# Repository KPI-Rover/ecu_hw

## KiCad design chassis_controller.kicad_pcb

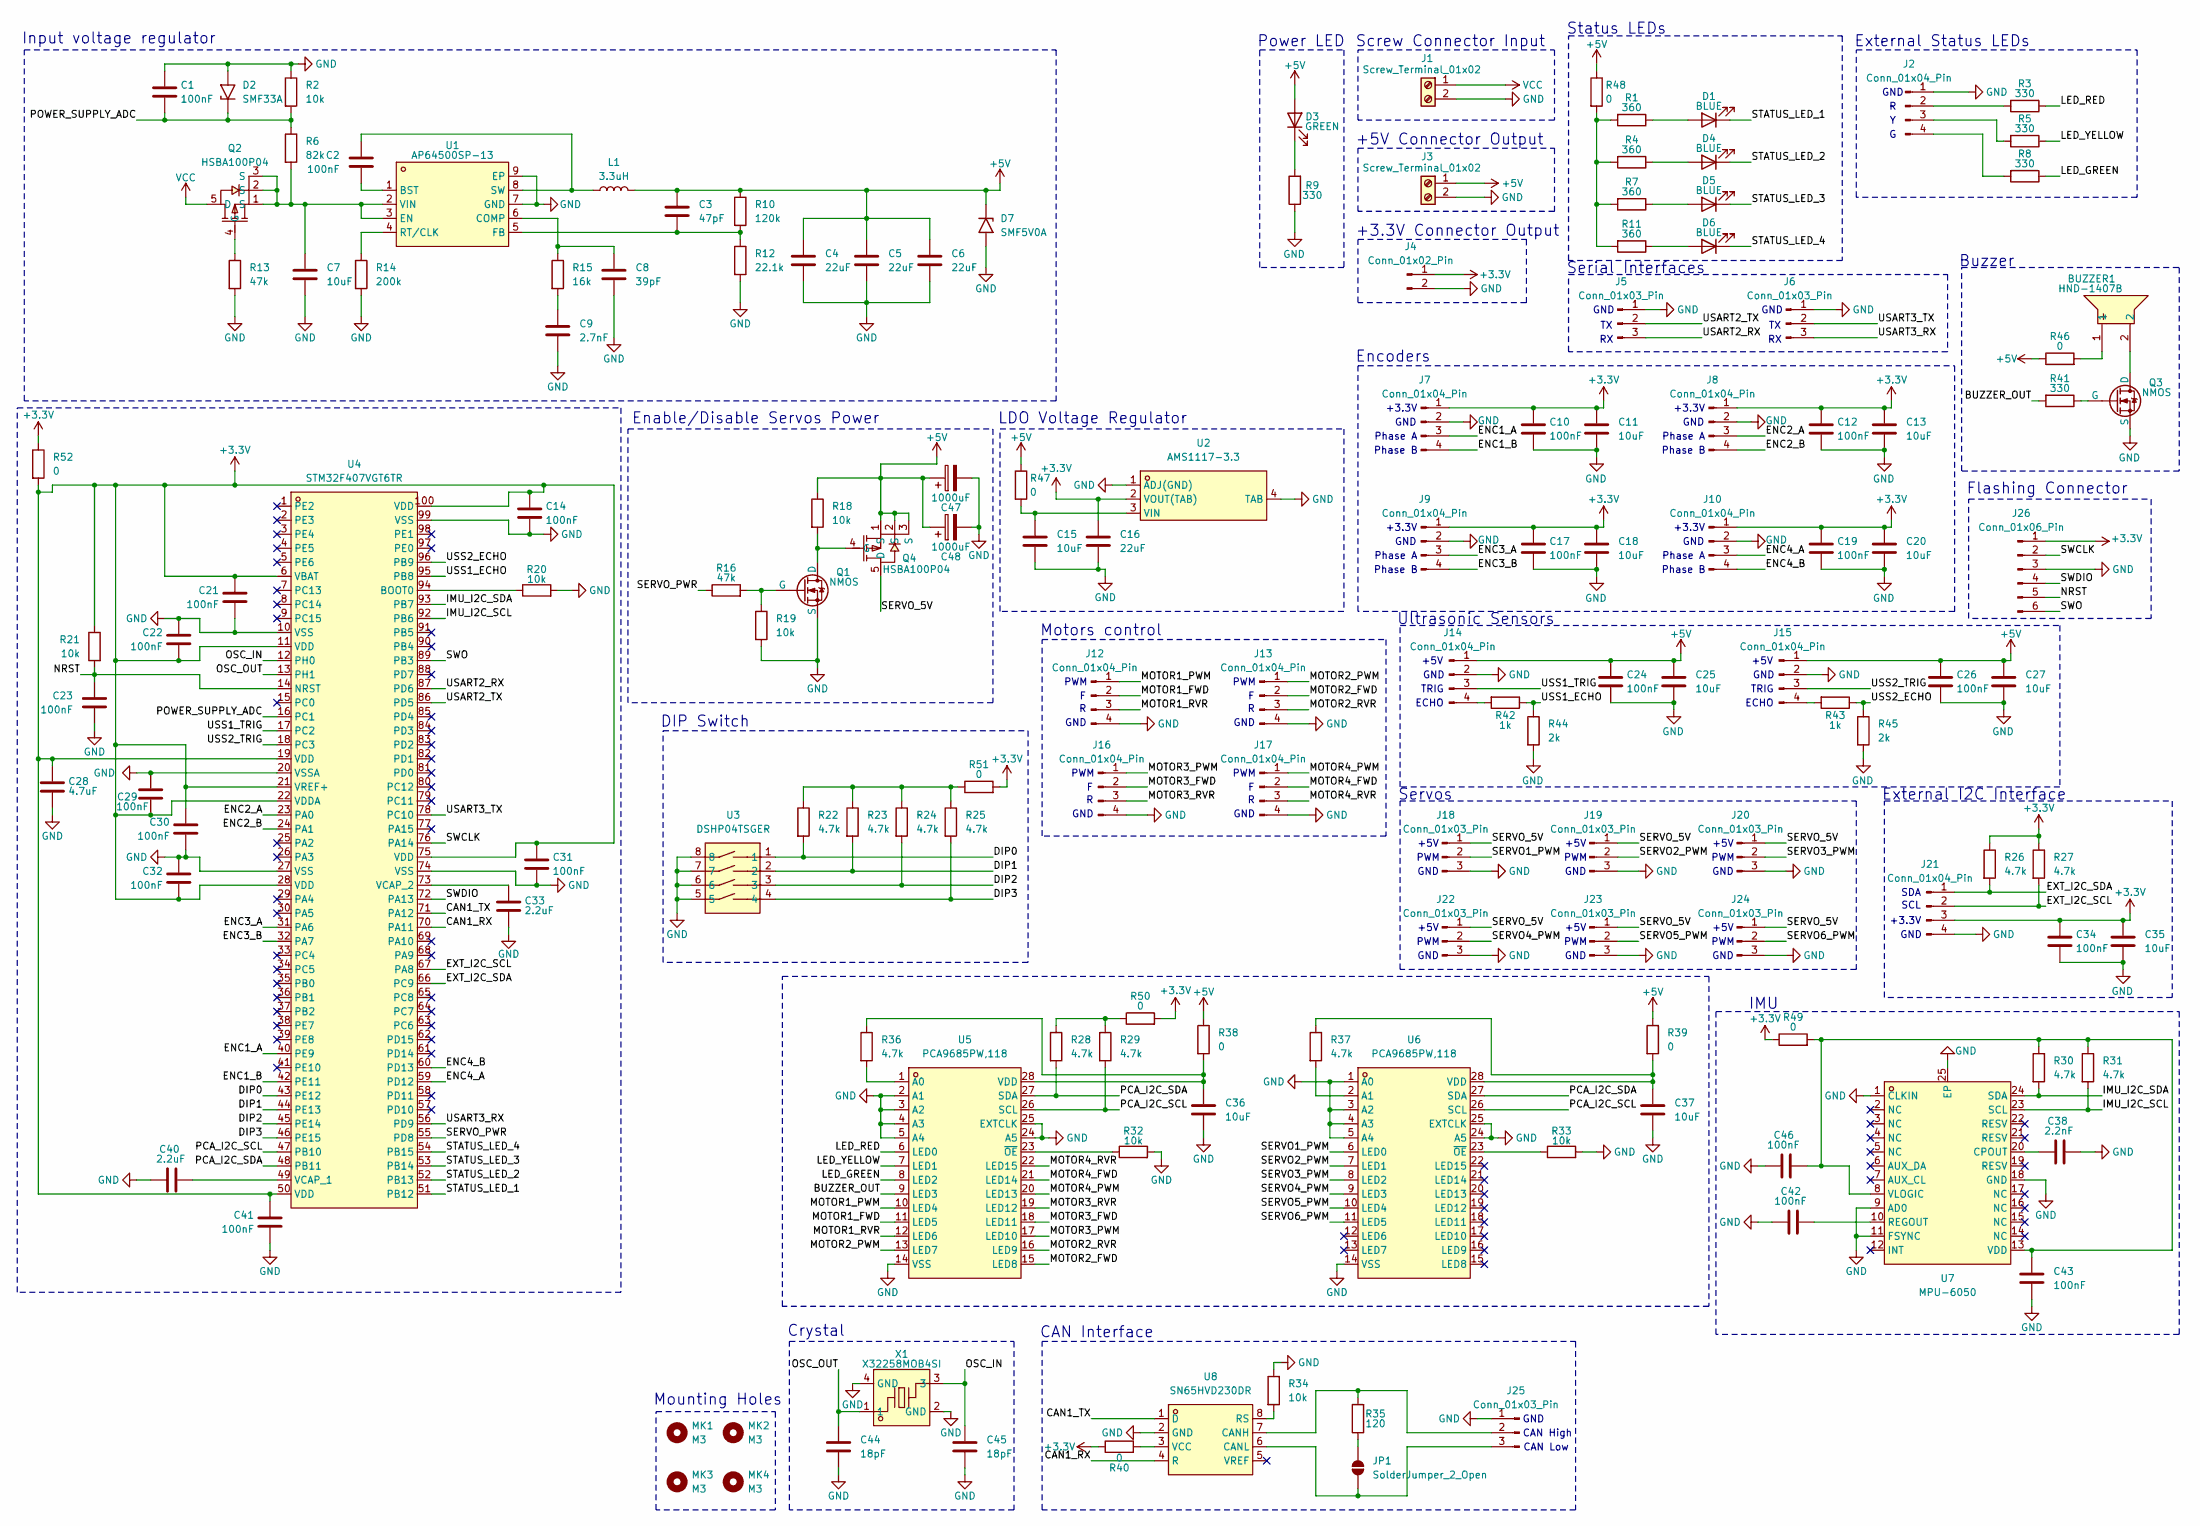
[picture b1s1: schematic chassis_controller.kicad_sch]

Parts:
BUZZER1: HND-1407B; BUZ-TH_BD14.1-P7.62-D1.0-FD; LCSC Part C115184
C1, C2, C10, C12, C14, C17, C19, C21, C22, C23, C24, C26, C29, C30, C31, C32, C34, C41, C42, C43, C46: 100nF; C_0805_2012Metric; LCSC Part C28233
C3: 47pF; C_0805_2012Metric; LCSC Part C107118
C4, C5, C6: 22uF; C_1206_3216Metric; LCSC Part C87996
C7, C15: 10uF; C_1206_3216Metric; LCSC Part C6119958
C8: 39pF; C_0805_2012Metric; LCSC Part C22470023
C9: 2.7nF; C_0805_2012Metric; LCSC Part C2918070
C11, C13, C18, C20, C25, C27, C35, C36, C37: 10uF; C_0805_2012Metric; LCSC Part C6119889
C16: 22uF; C_1206_3216Metric; LCSC Part C6119965
C28: 4.7uF; C_0805_2012Metric; LCSC Part C6119944
C33, C40: 2.2uF; C_0805_2012Metric; LCSC Part C125847
C38: 2.2nF; C_0805_2012Metric; LCSC Part C107146
C44, C45: 18pF; C_0805_2012Metric; LCSC Part C113825
C47, C48: 1000uF; CP_Radial_D10.0mm_P5.00mm; LCSC Part C439782
D1, D4, D5, D6: BLUE; LED_0805_2012Metric; LCSC Part C965817
D2: SMF33A; D_SMF; LCSC Part C37331473
D3: GREEN; LED_0805_2012Metric; LCSC Part C5875740
D7: SMF5V0A; D_SMF; LCSC Part C42387343
J1, J3: Screw_Terminal_01x02; CONN-TH_2P-P5.08; LCSC Part C3018698
J2, J7, J8, J9, J10, J12, J13, J14, J15, J16, J17, J21: Conn_01x04_Pin; JST_PH_B4B-PH-K_1x04_P2.00mm_Vertical; LCSC Part C131334
J4: Conn_01x02_Pin; JST_PH_B2B-PH-K_1x02_P2.00mm_Vertical; LCSC Part C131337
J5, J6, J18, J19, J20, J22, J23, J24, J25: Conn_01x03_Pin; JST_PH_B3B-PH-K_1x03_P2.00mm_Vertical; LCSC Part C131339
J26: Conn_01x06_Pin; JST_PH_B6B-PH-K_1x06_P2.00mm_Vertical; LCSC Part C131342
JP1: SolderJumper_2_Open; SolderJumper-2_P1.3mm_Open_Pad1.0x1.5mm
L1: 3.3uH; IND-SMD_L11.6-W10.1; LCSC Part C7587741
MK1, MK2, MK3, MK4: M3; MountingHole_3.2mm_M3_DIN965_Pad
Q1, Q3: NMOS; SOT-23; LCSC Part C347475
Q2, Q4: HSBA100P04; DFN-8_L5.7-W5.1-P1.27-LS6.1-BL-1; LCSC Part C2987717
R1, R4, R7, R11: 360; R_0805_2012Metric; LCSC Part C2930158
R2, R18, R19, R20, R21, R32, R33, R34: 10k; R_0805_2012Metric; LCSC Part C110775
R3, R5, R8, R9, R41: 330; R_0805_2012Metric; LCSC Part C2907321
R6: 82k; R_0805_2012Metric; LCSC Part C21571501
R10: 120k; R_0805_2012Metric; LCSC Part C103948
R12: 22.1k; R_0805_2012Metric; LCSC Part C2692772
R13, R16: 47k; R_0805_2012Metric; LCSC Part C2989281
R14: 200k; R_0805_2012Metric; LCSC Part C728645
R15: 16k; R_0805_2012Metric; LCSC Part C865809
R22, R23, R24, R25, R26, R27, R28, R29, R30, R31, R36, R37: 4.7k; R_0805_2012Metric; LCSC Part C2988931
R35: 120; R_0805_2012Metric; LCSC Part C17437
R38, R39, R40, R46, R47, R48, R49, R50, R51, R52: 0; R_0805_2012Metric; LCSC Part C17477
R42, R43: 1k; R_0805_2012Metric; LCSC Part C110774
R44, R45: 2k; R_0805_2012Metric; LCSC Part C2988894
U1: AP64500SP-13; SO-8_L4.9-W3.9-P1.27-LS6.0-BL-EP; LCSC Part C2070920
U2: AMS1117-3.3; SOT-223-4_L6.5-W3.5-P2.30-LS7.0-BR; LCSC Part C347222
U3: DSHP04TSGER; SW-SMD_8P-L6.7-W5.4-P1.27-LS8.4; LCSC Part C3293144
U4: STM32F407VGT6TR; LQFP-100_L14.0-W14.0-P0.50-LS16.0-BL; LCSC Part C919362
U5, U6: PCA9685PW,118; TSSOP-28_L9.7-W4.4-P0.65-LS6.4-TL; LCSC Part C2678753
U7: MPU-6050; QFN-24_L4.0-W4.0-P0.50-BL-EP2.7; LCSC Part C24112
U8: SN65HVD230DR; SOIC-8_L4.9-W3.9-P1.27-LS6.0-BL; LCSC Part C12084
X1: X32258MOB4SI; CRYSTAL-SMD_4P-L3.2-W2.5-BL; LCSC Part C2682775

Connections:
+3.3V: C10.1, C11.1, C12.1, C13.1, C14.1, C16.1, C17.1, C18.1, C19.1, C20.1, C21.1, C22.2, C28.2, C29.2, C30.1, C31.1, C32.2, C34.1, C35.1, C41.1, J4.1, J7.1, J8.1, J9.1, J10.1, J21.3, J26.1, R21.1, R26.1, R27.1, R40.1, R49.1, R50.2, R51.2, R52.1, R52.2, U2.2 (VOUT(TAB)), U4.6 (VBAT), U4.11 (VDD), U4.19 (VDD), U4.21 (VREF+), U4.22 (VDDA), U4.28 (VDD), U4.50 (VDD), U4.75 (VDD), U4.100 (VDD)
+5V: C3.1, C4.1, C5.1, C6.1, C24.1, C25.1, C26.1, C27.1, C47.1, C48.1, D3.2 (A), D7.1 (A1), J3.1, J14.1, J15.1, L1.2, Q4.1 (S), Q4.2 (S), Q4.3 (S), R10.1, R18.1, R38.1, R39.1, R46.1, R47.1, R48.1
/BUZZER_OUT: R41.2, U5.9 (LED3)
/CAN1_RX: U4.70 (PA11), U8.4 (R)
/CAN1_TX: U4.71 (PA12), U8.1 (D)
/DIP0: R22.2, U3.1, U4.43 (PE12)
/DIP1: R23.2, U3.2, U4.44 (PE13)
/DIP2: R24.2, U3.3, U4.45 (PE14)
/DIP3: R25.2, U3.4, U4.46 (PE15)
/ENC1_A: J7.3, U4.40 (PE9)
/ENC1_B: J7.4, U4.42 (PE11)
/ENC2_A: J8.3, U4.23 (PA0)
/ENC2_B: J8.4, U4.24 (PA1)
/ENC3_A: J9.3, U4.31 (PA6)
/ENC3_B: J9.4, U4.32 (PA7)
/ENC4_A: J10.3, U4.59 (PD12)
/ENC4_B: J10.4, U4.60 (PD13)
/EXT_I2C_SCL: J21.2, R27.2, U4.67 (PA8)
/EXT_I2C_SDA: J21.1, R26.2, U4.66 (PC9)
/IMU_I2C_SCL: R31.2, U4.92 (PB6), U7.23 (SCL)
/IMU_I2C_SDA: R30.2, U4.93 (PB7), U7.24 (SDA)
/LED_GREEN: R8.1, U5.8 (LED2)
/LED_RED: R3.1, U5.6 (LED0)
/LED_YELLOW: R5.1, U5.7 (LED1)
/MOTOR1_FWD: J12.2, U5.11 (LED5)
/MOTOR1_PWM: J12.1, U5.10 (LED4)
/MOTOR1_RVR: J12.3, U5.12 (LED6)
/MOTOR2_FWD: J13.2, U5.15 (LED8)
/MOTOR2_PWM: J13.1, U5.13 (LED7)
/MOTOR2_RVR: J13.3, U5.16 (LED9)
/MOTOR3_FWD: J16.2, U5.18 (LED11)
/MOTOR3_PWM: J16.1, U5.17 (LED10)
/MOTOR3_RVR: J16.3, U5.19 (LED12)
/MOTOR4_FWD: J17.2, U5.21 (LED14)
/MOTOR4_PWM: J17.1, U5.20 (LED13)
/MOTOR4_RVR: J17.3, U5.22 (LED15)
/NRST: C23.1, J26.5, R21.2, U4.14 (NRST)
/OSC_IN: C45.1, U4.12 (PH0), X1.3
/OSC_OUT: C44.1, U4.13 (PH1), X1.1
/PCA_I2C_SCL: R29.2, U4.47 (PB10), U5.26 (SCL), U6.26 (SCL)
/PCA_I2C_SDA: R28.2, U4.48 (PB11), U5.27 (SDA), U6.27 (SDA)
/POWER_SUPPLY_ADC: C1.2, D2.1 (A1), R2.2, R6.1, U4.16 (PC1)
/SERVO1_PWM: J18.2, U6.6 (LED0)
/SERVO2_PWM: J19.2, U6.7 (LED1)
/SERVO3_PWM: J20.2, U6.8 (LED2)
/SERVO4_PWM: J22.2, U6.9 (LED3)
/SERVO5_PWM: J23.2, U6.10 (LED4)
/SERVO6_PWM: J24.2, U6.11 (LED5)
/SERVO_5V: J18.1, J19.1, J20.1, J22.1, J23.1, J24.1, Q4.5 (D)
/SERVO_PWR: R16.1, U4.55 (PD8)
/STATUS_LED_1: D1.1 (K), U4.51 (PB12)
/STATUS_LED_2: D4.1 (K), U4.52 (PB13)
/STATUS_LED_3: D5.1 (K), U4.53 (PB14)
/STATUS_LED_4: D6.1 (K), U4.54 (PB15)
/SWCLK: J26.2, U4.76 (PA14)
/SWDIO: J26.4, U4.72 (PA13)
/SWO: J26.6, U4.89 (PB3)
/USART2_RX: J5.3, U4.87 (PD6)
/USART2_TX: J5.2, U4.86 (PD5)
/USART3_RX: J6.3, U4.56 (PD9)
/USART3_TX: J6.2, U4.78 (PC10)
/USS1_ECHO: R42.1, R44.1, U4.95 (PB8)
/USS1_TRIG: J14.3, U4.17 (PC2)
/USS2_ECHO: R43.1, R45.1, U4.96 (PB9)
/USS2_TRIG: J15.3, U4.18 (PC3)
GND: C1.1, C4.2, C5.2, C6.2, C7.2, C8.2, C9.2, C10.2, C11.2, C12.2, C13.2, C14.2, C15.2, C16.2, C17.2, C18.2, C19.2, C20.2, C21.2, C22.1, C23.2, C24.2, C25.2, C26.2, C27.2, C28.1, C29.1, C30.2, C31.2, C32.1, C33.1, C34.2, C35.2, C36.2, C37.2, C38.2, C40.1, C41.2, C42.1, C43.2, C44.2, C45.2, C46.1, C47.2, C48.2, D2.2 (A2), D7.2 (A2), J1.2, J2.1, J3.2, J4.2, J5.1, J6.1, J7.2, J8.2, J9.2, J10.2, J12.4, J13.4, J14.2, J15.2, J16.4, J17.4, J18.3, J19.3, J20.3, J21.4, J22.3, J23.3, J24.3, J25.1, J26.3, Q1.3 (S), Q3.3 (S), R2.1, R9.1, R12.2, R13.2, R14.2, R19.2, R20.2, R32.2, R33.2, R34.1, R44.2, R45.2, U1.7 (GND), U1.9 (EP), U2.1 (ADJ(GND)), U2.4 (TAB), U3.5, U3.6, U3.7, U3.8, U4.10 (VSS), U4.20 (VSSA), U4.27 (VSS), U4.74 (VSS), U4.99 (VSS), U5.2 (A1), U5.3 (A2), U5.4 (A3), U5.5 (A4), U5.14 (VSS), U5.24 (A5), U5.25 (EXTCLK), U6.1 (A0), U6.3 (A2), U6.4 (A3), U6.5 (A4), U6.14 (VSS), U6.24 (A5), U6.25 (EXTCLK), U7.1 (CLKIN), U7.9 (AD0), U7.11 (FSYNC), U7.18 (GND), U7.25 (EP), U8.2 (GND), X1.2 (GND), X1.4 (GND)
unnamed: BUZZER1.1, R46.2
unnamed: C9.1, R15.2
unnamed: D1.2 (A), R1.1
unnamed: D3.1 (K), R9.2
unnamed: D4.2 (A), R4.1
unnamed: D5.2 (A), R7.1
unnamed: D6.2 (A), R11.1
unnamed: J2.2, R3.2
unnamed: J2.3, R5.2
unnamed: J2.4, R8.2
unnamed: J14.4, R42.2
unnamed: J15.4, R43.2
unnamed: J25.2, R35.2, U8.7 (CANH)
unnamed: J25.3, JP1.2 (B), U8.6 (CANL)
unnamed: JP1.1 (A), R35.1
unnamed: Q1.1 (D), Q4.4 (G), R18.2
unnamed: Q1.2 (G), R16.2, R19.1
unnamed: Q2.4 (G), R13.1
unnamed: BUZZER1.2, Q3.1 (D)
unnamed: Q3.2 (G), R41.1
unnamed: R1.2, R4.2, R7.2, R11.2, R48.2
unnamed: R22.1, R23.1, R24.1, R25.1, R51.1
unnamed: R28.1, R29.1, R50.1
unnamed: C2.2, U1.1 (BST)
unnamed: C8.1, R15.1, U1.6 (COMP)
unnamed: C7.1, Q2.1 (S), Q2.2 (S), Q2.3 (S), R6.2, U1.2 (VIN), U1.3 (EN)
unnamed: C3.2, R10.2, R12.1, U1.5 (FB)
unnamed: R14.1, U1.4 (RT/CLK)
unnamed: C2.1, L1.1, U1.8 (SW)
unnamed: C15.1, R47.2, U2.3 (VIN)
unnamed: R20.1, U4.94 (BOOT0)
unnamed: C40.2, U4.49 (VCAP_1)
unnamed: C33.2, U4.73 (VCAP_2)
unnamed: R36.2, U5.1 (A0)
unnamed: C36.1, R36.1, R38.2, U5.28 (VDD)
unnamed: R32.1, U5.23 (~OE)
unnamed: R37.2, U6.2 (A1)
unnamed: C37.1, R37.1, R39.2, U6.28 (VDD)
unnamed: R33.1, U6.23 (~OE)
unnamed: C38.1, U7.20 (CPOUT)
unnamed: C42.2, U7.10 (REGOUT)
unnamed: C43.1, C46.2, R30.1, R31.1, R49.2, U7.8 (VLOGIC), U7.13 (VDD)
unnamed: R34.2, U8.8 (RS)
unnamed: R40.2, U8.3 (VCC)
VCC: J1.1, Q2.5 (D)

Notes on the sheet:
GND
Screw Connector Input
Phase B
PWM
Flashing Connector
External I2C Interface
Status LEDs
+5V
Power LED
Phase A
+3.3V
+5V Connector Output
External Status LEDs
Mounting Holes
SDA
Buzzer
IMU
CAN Low
CAN Interface
Enable/Disable Servos Power
Serial Interfaces
DIP Switch
Encoders
Ultrasonic Sensors
LDO Voltage Regulator
ECHO
TRIG
+3.3V Connector Output
Crystal
Motors control
CAN High
Input voltage regulator
Servos
SCL

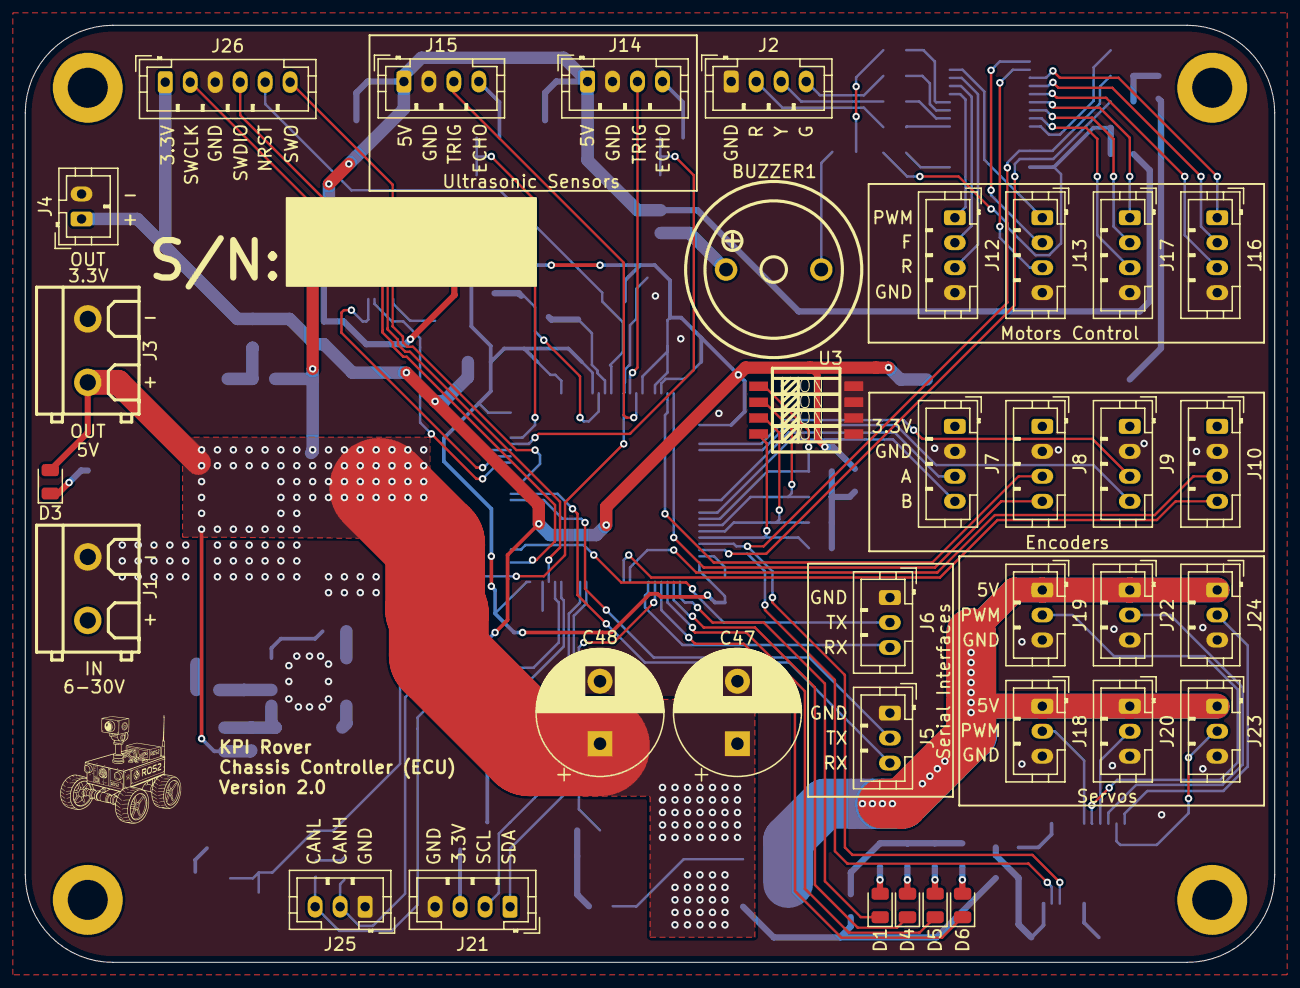
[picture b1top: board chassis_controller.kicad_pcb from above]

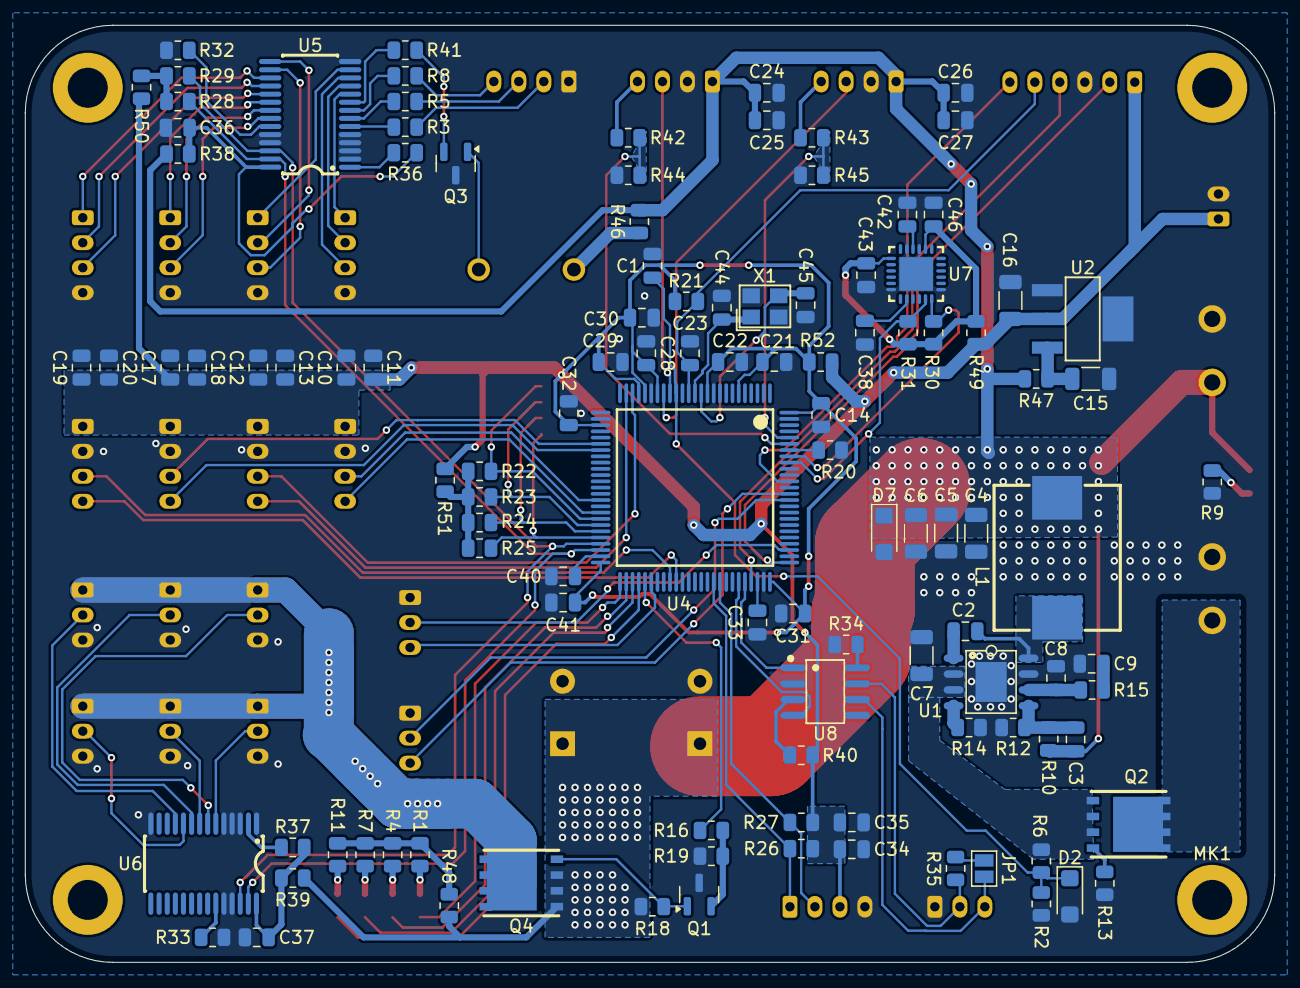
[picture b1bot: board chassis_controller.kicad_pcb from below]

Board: 2 copper layers, 100.0 x 75.0 mm, 150 parts (113 on the bottom side), 111 nets.

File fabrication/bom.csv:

"Reference","Qty","Value","LCSC Part"
"BUZZER1","1","HND-1407B","C115184"
"C1,C2,C10,C12,C14,C17,C19,C21,C22,C23,C24,C26,C29,C30,C31,C32,C34,C41,C42,C43,C46","21","100nF","C28233"
"C3","1","47pF","C107118"
"C4,C5,C6","3","22uF","C87996"
"C7,C15","2","10uF","C6119958"
"C8","1","39pF","C22470023"
"C9","1","2.7nF","C2918070"
"C11,C13,C18,C20,C25,C27,C35,C36,C37","9","10uF","C6119889"
"C16","1","22uF","C6119965"
"C28","1","4.7uF","C6119944"
"C33,C40","2","2.2uF","C125847"
"C38","1","2.2nF","C107146"
"C44,C45","2","18pF","C113825"
"C47,C48","2","1000uF","C439782"
"D1,D4,D5,D6","4","BLUE","C965817"
"D2","1","SMF33A","C37331473"
"D3","1","GREEN","C5875740"
"D7","1","SMF5V0A","C42387343"
"J1,J3","2","Screw_Terminal_01x02","C3018698"
"J2,J7,J8,J9,J10,J12,J13,J14,J15,J16,J17,J21","12","Conn_01x04_Pin","C131334"
"J4","1","Conn_01x02_Pin","C131337"
"J5,J6,J18,J19,J20,J22,J23,J24,J25","9","Conn_01x03_Pin","C131339"
"J26","1","Conn_01x06_Pin","C131342"
"JP1,MK1,MK2,MK3,MK4","5","M3,SolderJumper_2_Open",""
"L1","1","3.3uH","C7587741"
"Q1,Q3","2","NMOS","C347475"
"Q2,Q4","2","HSBA100P04","C2987717"
"R1,R4,R7,R11","4","360","C2930158"
"R2,R18,R19,R20,R21,R32,R33,R34","8","10k","C110775"
"R3,R5,R8,R9,R41","5","330","C2907321"
"R6","1","82k","C21571501"
"R10","1","120k","C103948"
"R12","1","22.1k","C2692772"
"R13,R16","2","47k","C2989281"
"R14","1","200k","C728645"
"R15","1","16k","C865809"
"R22,R23,R24,R25,R26,R27,R28,R29,R30,R31,R36,R37","12","4.7k","C2988931"
"R35","1","120","C17437"
"R38,R39,R40,R46,R47,R48,R49,R50,R51,R52","10","0","C17477"
"R42,R43","2","1k","C110774"
"R44,R45","2","2k","C2988894"
"U1","1","AP64500SP-13","C2070920"
"U2","1","AMS1117-3.3","C347222"
"U3","1","DSHP04TSGER","C3293144"
"U4","1","STM32F407VGT6TR","C919362"
"U5,U6","2","PCA9685PW,118","C2678753"
"U7","1","MPU-6050","C24112"
"U8","1","SN65HVD230DR","C12084"
"X1","1","X32258MOB4SI","C2682775"

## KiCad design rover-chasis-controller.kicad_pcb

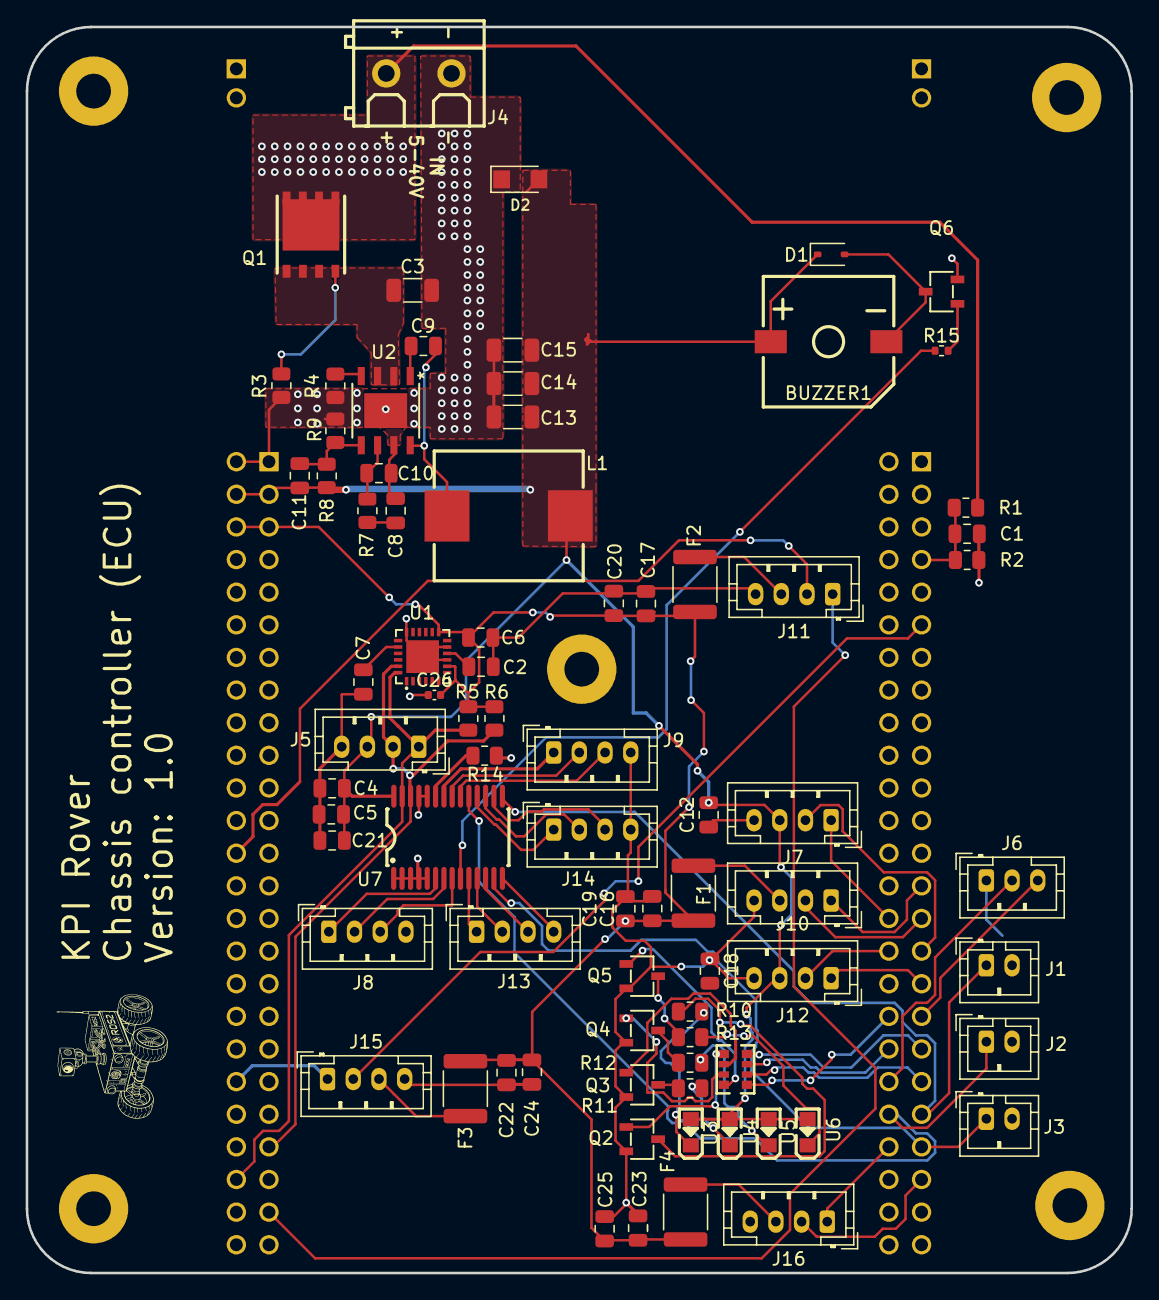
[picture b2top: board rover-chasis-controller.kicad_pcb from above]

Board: 2 copper layers, 86.0 x 97.0 mm, 85 parts (1 on the bottom side), 70 nets.

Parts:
BUZZER1: YS-SBZ9650DYB05_C409830; BUZ-SMD_L9.6-W9.6-LS10.0-R
C1, C2, C4, C6, C9, C12, C18, C19, C20, C24, C25: 0.1uF; C_0805_2012Metric
C3: 10uFx50V; C_1206_3216Metric
C5, C16, C17, C21, C22, C23: 10uFx16V; C_0805_2012Metric
C7: 2.2nF; C_0805_2012Metric
C8: 2.7nF; C_0805_2012Metric
C10: 39pF; C_0805_2012Metric
C11: 47pF; C_0805_2012Metric
C13, C14, C15: 22uF; C_1206_3216Metric
C26: 10nF; C_0402_1005Metric
D1: D; D_SOD-323
D2: SMF5V0A; D_SMF
F1, F2, F3, F4: Fuse; Fuse_1812_4532Metric
J1: External LED (Green); JST_PH_B2B-PH-K_1x02_P2.00mm_Vertical
J2: External LED (Yellow); JST_PH_B2B-PH-K_1x02_P2.00mm_Vertical
J3: External LED (Red); JST_PH_B2B-PH-K_1x02_P2.00mm_Vertical
J4: Screw_Terminal_01x02; CONN-TH_2P-P5.08
J5: Compass Connection (I2C); JST_PH_B4B-PH-K_1x04_P2.00mm_Vertical
J6: TTL; JST_PH_B3B-PH-K_1x03_P2.00mm_Vertical
J7, J12: Ultrasonic Sensor Inputs; JST_PH_B4B-PH-K_1x04_P2.00mm_Vertical
J8, J9, J13, J14: Motor control; JST_PH_B4B-PH-K_1x04_P2.00mm_Vertical
J10, J11, J15, J16: Encoder; JST_PH_B4B-PH-K_1x04_P2.00mm_Vertical
L1: 3.3uH; IND-SMD_L11.6-W10.1
MK1, MK2, MK3, MK4, MK5: M2.5; MountingHole_2.7mm_M2.5_Pad
Q1: HSBA100P04_C2987717; DFN-8_L5.7-W5.1-P1.27-LS6.1-BL-1
Q2, Q3, Q4, Q5, Q6: MMBT3904_C181119; SOT-23-3_L2.9-W1.6-P1.90-LS2.8-BR
R1: 100k; R_0805_2012Metric
R2: 22k; R_0805_2012Metric
R3: 47k; R_0805_2012Metric
R4: 200k; R_0805_2012Metric
R5, R6: 4.3k; R_0805_2012Metric
R7: 16k; R_0805_2012Metric
R8: 120k; R_0805_2012Metric
R9: 22.1k; R_0805_2012Metric
R10, R11, R12, R13: 220; R_0805_2012Metric
R14: 10k; R_0805_2012Metric
R15: 1k; R_0402_1005Metric
RN1: 4D03WGJ0102T5E (1k); RES-ARRAY-SMD_0603-8P-L3.2-W1.6-BL
TB1: STM32F4DISCOVERY; MODULE_STM32F4DISCOVERY
U1: MPU-6050_C24112; QFN-24_L4.0-W4.0-P0.50-BL-EP2.6
U2: AP64500; AP64500SP-13
U3, U4, U5, U6: APT2012LVBC/D; LED-SMD_L2.0-W1.3-R-RD
U7: PCA9685PW,118; TSSOP-28_L9.7-W4.4-P0.65-LS6.4-TL

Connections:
/BUZZER_OUT: R15.1, U7.9 (LED3)
/ENC1_A: J10.1, TB1.P1_27 (PE9)
/ENC1_B: J10.2, TB1.P1_29 (PE11)
/ENC2_A: J15.1, TB1.P2_40 (PA15)
/ENC2_B: J15.2, TB1.P1_11 (PA1)
/ENC3_A: J11.1, TB1.P2_47 (PC6)
/ENC3_B: J11.2, TB1.P2_26 (PB5)
/ENC4_A: J16.1, TB1.P1_44 (PD12)
/ENC4_B: J16.2, TB1.P1_45 (PD13)
/LED_BLUE_1: RN1.8, TB1.P1_37 (PB13)
/LED_BLUE_2: RN1.7, TB1.P1_38 (PB14)
/LED_BLUE_3: RN1.6, TB1.P1_39 (PB15)
/LED_BLUE_4: RN1.5, TB1.P1_36 (PB12)
/LED_Collector_1: Q2.3, R10.2
/LED_Collector_2: Q3.3, R11.2
/LED_Collector_3: Q4.3, R12.2
/LED_Collector_4: Q5.3, R13.2
/LED_GREEN: J1.1, TB1.P1_41 (PD9), U7.15 (LED8)
/LED_RED: J3.1, TB1.P1_43 (PD11), U7.13 (LED7)
/LED_YELLOW: J2.1, TB1.P1_42 (PD10), U7.19 (LED12)
/MOTOR1_FWD: J8.2, U7.7 (LED1)
/MOTOR1_PWM: J8.1, U7.6 (LED0)
/MOTOR1_RVR: J8.3, U7.8 (LED2)
/MOTOR2_FWD: J13.2, U7.11 (LED5)
/MOTOR2_PWM: J13.1, U7.10 (LED4)
/MOTOR2_RVR: J13.3, U7.12 (LED6)
/MOTOR3_FWD: J9.2, U7.21 (LED14)
/MOTOR3_PWM: J9.1, U7.22 (LED15)
/MOTOR3_RVR: J9.3, U7.20 (LED13)
/MOTOR4_FWD: J14.2, U7.17 (LED10)
/MOTOR4_PWM: J14.1, U7.18 (LED11)
/MOTOR4_RVR: J14.3, U7.16 (LED9)
/POWER_SUPPLY_ADC: C1.2, R1.2, R2.1, TB1.P1_7 (PC1)
/SCL: J5.2, R6.2, TB1.P2_43 (PA8), U1.23 (SCL), U7.26 (SCL)
/SDA: J5.1, R5.2, TB1.P2_46 (PC9), U1.24 (SDA), U7.27 (SDA)
/TTL_RX: J6.3, TB1.P1_35 (PB11)
/TTL_TX: J6.2, TB1.P1_40 (PD8)
/US_SENSOR1_ECHO: J7.2, TB1.P1_31 (PE13)
/US_SENSOR1_TRIG: J7.1, TB1.P1_30 (PE12)
/US_SENSOR2_ECHO: J12.2, TB1.P1_32 (PE14)
/US_SENSOR2_TRIG: J12.1, TB1.P1_33 (PE15)
/transistor_array4/B1: Q2.1, RN1.1
/transistor_array4/B2: Q3.1, RN1.2
/transistor_array4/B3: Q4.1, RN1.3
/transistor_array4/B4: Q5.1, RN1.4
GND: C1.1, C2.1, C3.2, C4.1, C5.1, C6.1, C7.2, C8.2, C10.2, C12.1, C13.2, C14.2, C15.2, C16.1, C17.1, C18.1, C19.1, C20.1, C21.2, C22.1, C23.1, C24.1, C25.1, C26.1, D2.1 (A1), J1.2, J2.2, J3.2, J4.2, J5.4, J6.1, J7.4, J8.4, J9.4, J10.4, J11.4, J12.4, J13.4, J14.4, J15.4, J16.4, Q2.2, Q3.2, Q4.2, Q5.2, Q6.2, R2.2, R3.2, R4.2, R9.2, R14.1, TB1.P1_1 (GND), TB1.P1_2 (GND), TB1.P1_5 (GND), TB1.P1_23 (GND), TB1.P1_49 (GND), TB1.P1_50 (GND), TB1.P2_1 (GND), TB1.P2_2 (GND), TB1.P2_49 (GND), TB1.P2_50 (GND), U1.9 (AD0), U1.11 (FSYNC), U1.18 (GND), U1.25 (EP), U2.7 (GND), U7.1 (A0), U7.2 (A1), U7.3 (A2), U7.4 (A3), U7.5 (A4), U7.14 (VSS), U7.24 (A5), U7.25 (EXTCLK)
unnamed: BUZZER1.2 (-), D1.2 (A), Q6.3
unnamed: C8.1, R7.2
unnamed: F1.1, J10.3
unnamed: F2.1, J11.3
unnamed: F3.1, J15.3
unnamed: F4.1, J16.3
unnamed: Q1.4 (G), R3.1
unnamed: Q6.1, R15.2
unnamed: TB1.P1_3 (VDD), TB1.P1_4 (VDD), TB1.P2_22 (VDD)
unnamed: C7.1, U1.20 (CPOUT)
unnamed: C2.2, U1.10 (REGOUT)
unnamed: C9.1, U2.1 (BST)
unnamed: C10.1, R7.1, U2.6 (COMP)
unnamed: C11.2, R8.2, R9.1, U2.5 (FB)
unnamed: R4.1, U2.4 (RT/CLK)
unnamed: C9.2, L1.1, U2.8 (SW)
unnamed: R10.1, U3.2 (K)
unnamed: R11.1, U4.2 (K)
unnamed: R12.1, U5.2 (K)
unnamed: R13.1, U6.2 (K)
unnamed: R14.2, U7.23 (~OE)
VCC (5V): BUZZER1.1 (+), C4.2, C5.2, C11.1, C12.2, C13.1, C14.1, C15.1, C18.2, C21.1, D1.1 (K), D2.2 (A2), J5.3, J7.3, J12.3, L1.2, R8.1, TB1.P2_3 (5V), TB1.P2_4 (5V), U3.1 (A), U4.1 (A), U5.1 (A), U6.1 (A), U7.28 (VDD)
VCC (12V): J4.1, Q1.5 (D), R1.1
VDD (3V): C6.2, C16.2, C17.2, C19.2, C20.2, C22.2, C23.2, C24.2, C25.2, C26.2, F1.2, F2.2, F3.2, F4.2, R5.1, R6.1, TB1.P2_5 (3V), TB1.P2_6 (3V), U1.8 (VLOGIC), U1.13 (VDD)

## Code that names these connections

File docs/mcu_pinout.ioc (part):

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Mcu.Name=STM32F407V(E-G)Tx
Mcu.Package=LQFP100
Mcu.UserName=STM32F407VGTx
PA0-WKUP.GPIOParameters=GPIO_Label
PA0-WKUP.GPIO_Label=ENC2_A
PA0-WKUP.Signal=S_TIM5_CH1
PA1.GPIOParameters=GPIO_Label
PA1.GPIO_Label=ENC2_B
PA1.Signal=S_TIM5_CH2
PA11.Mode=CAN_Activate
PA11.Signal=CAN1_RX
PA12.Mode=CAN_Activate
PA12.Signal=CAN1_TX
PA13.Mode=Trace_Asynchronous_SW
PA13.Signal=SYS_JTMS-SWDIO
PA14.Mode=Trace_Asynchronous_SW
PA14.Signal=SYS_JTCK-SWCLK
PA6.GPIOParameters=GPIO_Label
PA6.GPIO_Label=ENC3_A
PA6.Signal=S_TIM3_CH1
PA7.GPIOParameters=GPIO_Label
PA7.GPIO_Label=ENC3_B
PA7.Signal=S_TIM3_CH2
PA8.GPIOParameters=GPIO_Label
PA8.GPIO_Label=EXT_I2C_SCL
PA8.Mode=I2C
PA8.Signal=I2C3_SCL
PB10.GPIOParameters=GPIO_Label
PB10.GPIO_Label=PCA_I2C_SCL
PB10.Mode=I2C
PB10.Signal=I2C2_SCL
PB11.GPIOParameters=GPIO_Label
PB11.GPIO_Label=PCA_I2C_SDA
PB11.Mode=I2C
PB11.Signal=I2C2_SDA
PB12.GPIOParameters=GPIO_Label
PB12.GPIO_Label=STATUS_LED_1
PB12.Signal=GPIO_Output
PB13.GPIOParameters=GPIO_Label
PB13.GPIO_Label=STATUS_LED_2
PB13.Signal=GPIO_Output
PB14.GPIOParameters=GPIO_Label
PB14.GPIO_Label=STATUS_LED_3
PB14.Signal=GPIO_Output
PB15.GPIOParameters=GPIO_Label
PB15.GPIO_Label=STATUS_LED_4
PB15.Signal=GPIO_Output
PB3.Mode=Trace_Asynchronous_SW
PB3.Signal=SYS_JTDO-SWO
PB6.GPIOParameters=GPIO_Label
PB6.GPIO_Label=IMU_I2C_SCL
PB6.Mode=I2C
PB6.Signal=I2C1_SCL
PB7.GPIOParameters=GPIO_Label
PB7.GPIO_Label=IMU_I2C_SDA
PB7.Mode=I2C
PB7.Signal=I2C1_SDA
PB8.GPIOParameters=GPIO_Label
PB8.GPIO_Label=USS1_ECHO
PB8.Signal=S_TIM10_CH1
PB9.GPIOParameters=GPIO_Label
PB9.GPIO_Label=USS2_ECHO
PB9.Signal=S_TIM11_CH1
PC1.GPIOParameters=GPIO_Label
PC1.GPIO_Label=POWER_SUPPLY_ADC
PC1.Signal=ADCx_IN11
PC10.Mode=Asynchronous
PC10.Signal=USART3_TX
PC2.GPIOParameters=GPIO_Label
PC2.GPIO_Label=USS1_TRIG
PC2.Signal=GPIO_Output
PC3.GPIOParameters=GPIO_Label
PC3.GPIO_Label=USS2_TRIG
PC3.Signal=GPIO_Output
PC9.GPIOParameters=GPIO_Label
PC9.GPIO_Label=EXT_I2C_SDA
PC9.Mode=I2C
PC9.Signal=I2C3_SDA
PD12.GPIOParameters=GPIO_Label
PD12.GPIO_Label=ENC4_A
PD12.Signal=S_TIM4_CH1
PD13.GPIOParameters=GPIO_Label
PD13.GPIO_Label=ENC4_B
PD13.Signal=S_TIM4_CH2
PD5.Mode=Asynchronous
PD5.Signal=USART2_TX
PD6.Mode=Asynchronous
PD6.Signal=USART2_RX
PD8.GPIOParameters=GPIO_Label
PD8.GPIO_Label=SERVO_PWR
PD8.Signal=GPIO_Output
PD9.Mode=Asynchronous
PD9.Signal=USART3_RX
PE11.GPIOParameters=GPIO_Label
PE11.GPIO_Label=ENC1_B
PE11.Signal=S_TIM1_CH2
PE12.GPIOParameters=GPIO_Label
PE12.GPIO_Label=DIP0
PE12.Signal=GPIO_Input
PE13.GPIOParameters=GPIO_Label
PE13.GPIO_Label=DIP1
PE13.Signal=GPIO_Input
PE14.GPIOParameters=GPIO_Label
PE14.GPIO_Label=DIP2
PE14.Signal=GPIO_Input
PE15.GPIOParameters=GPIO_Label
PE15.GPIO_Label=DIP3
PE15.Signal=GPIO_Input
PE9.GPIOParameters=GPIO_Label
PE9.GPIO_Label=ENC1_A
PE9.Signal=S_TIM1_CH1
PH0-OSC_IN.Mode=HSE-External-Oscillator
PH0-OSC_IN.Signal=RCC_OSC_IN
PH1-OSC_OUT.Mode=HSE-External-Oscillator
PH1-OSC_OUT.Signal=RCC_OSC_OUT
RCC.HSE_VALUE=25000000
RCC.SYSCLKFreq_VALUE=16000000
board=custom

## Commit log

2024-11-14 Translate requirements for chassis ECU to English
2024-11-14 Translate requirements for power HAT to English.
2024-11-14 Translate README.md to English
2025-02-09 Clean up
2025-03-07 Issue #1: Initial setup
2025-03-19 Issue #1: Major revision
2025-04-02 Issue #1: Resistor arrays and refactoring
2025-04-13 Issue #1: added Ethernet, MPU, reworked LEDs
2025-04-14 Issue #1: Replaced resistors, fuses, and diode with SMD ones
2025-04-30 Issue #1: Added XTAL and RJ45 Connector
2025-05-28 Issue #1: Populated pins, small fixes
2025-10-28 Issue #1: Sketched a rough preliminary PCB design layout
2025-11-07 KiCad project upload
2026-01-06 Issue #1: Revised possible PCB design
2026-01-08 Issue #1: Updated PCB layout — mounting holes, silk screen, and DRC fixes
2026-01-11 Issue #1: Refactored PCB design
2026-01-11 Issue #1: Corrected some mistakes
2026-01-12 Issue #1: Improved power supply zoning
2026-01-13 Issue #1: Corrected some mistakes
    Solved short circuit problems, replaced components smaller that 0805, adjusted references on the pcb design, connected TTL connector to STM32, added missing schematic to measure input voltage
2026-01-15 Issue #1: Replaced out-of-stock components
2026-01-15 Issue #1: Removed unnecessary fields inside components
2026-01-18 Issue #1: Prepare for production
2026-01-30 Issue #4: Define requirements and MCU pinout
2026-02-25 Add improvements to project
2026-03-29 Update project
2026-04-03 Board malfunction fixes
    - Changed F1-F4, R5, R6 to 3V (previous 5V caused failure).
    - Connected STM32DISC1 to 5V and 3V outputs/inputs
    - Moved SDA to PC9 (was PA9) and ENC3_A to PC6 (was PC3).
    - Redesigned MPU6050 layout to resolve stability and connectivity issues.
    - Isolated PCA6587 buzzer with a transistor.
2026-04-06 Issue #4: Improve DC-DC layout. Prepare for production.
2026-04-06 Remove backups
2026-04-06 Update gitignore
2026-04-06 Fix servo power line
